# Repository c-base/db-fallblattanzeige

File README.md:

# db-fallblattanzeige
A Fallblattfahrzielanzeige of the Deutsche Bahn

  - [Demo video](https://www.youtube.com/watch?v=KNWKdqRn240)
  - [Hackaday Project](https://hackaday.io/project/9070-fallblattfahrzielanzeige-of-s-bahn-berlin)

Daemon ist unter: https://github.com/c-base/db-fallblattanzeige-web/roloboxd/

Web-Interface-Repo ist unter: https://github.com/c-base/db-fallblattanzeige-web

Architektur-Skizze: https://www.dropbox.com/s/tzrm99uehv5yp3d/whiteboard.png?dl=0

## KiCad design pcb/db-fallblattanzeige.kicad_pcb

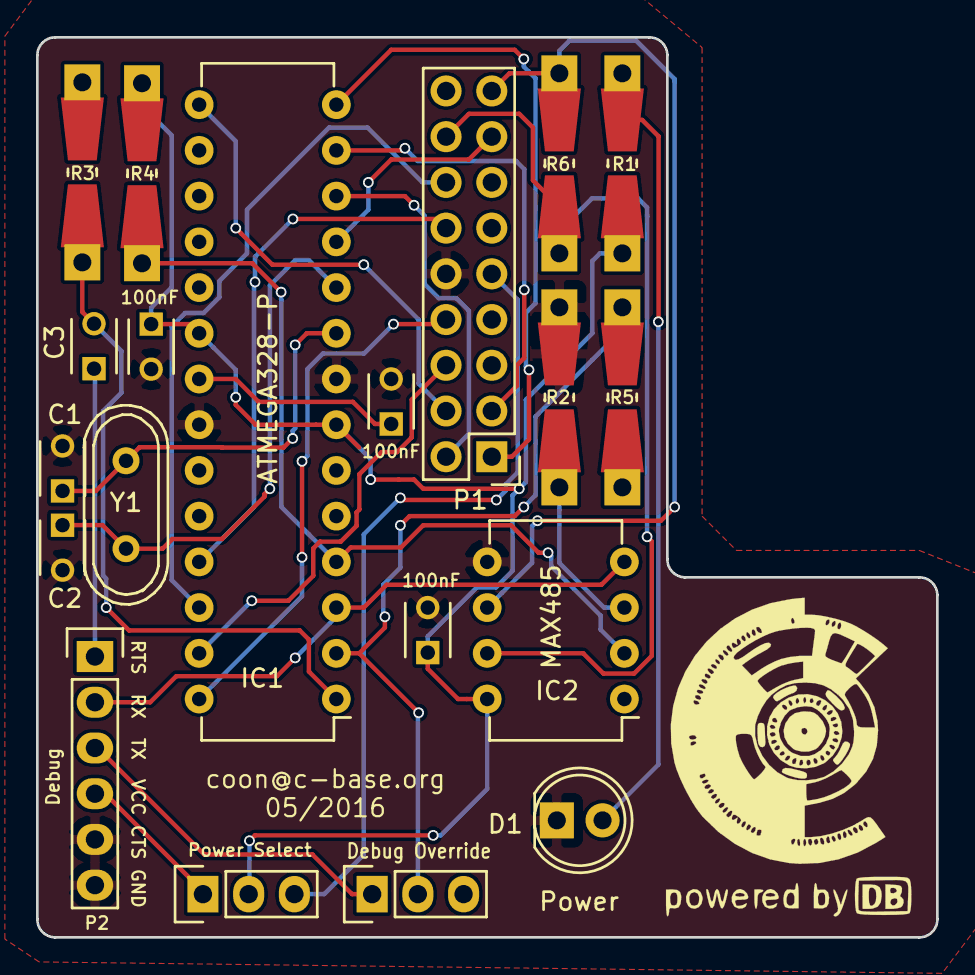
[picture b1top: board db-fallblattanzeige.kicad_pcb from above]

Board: 2 copper layers, 50.0 x 50.0 mm, 20 parts (0 on the bottom side), 27 nets.

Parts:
100nF, 100nF#2, 100nF#3: C; C_Disc_D3_P2.5
C1, C2: 22pF; C_Disc_D3_P2.5
C3: 100nF; C_Disc_D3_P2.5
D1: Power LED (Green); LED-5MM
IC1: ATMEGA328-P; DIP-28_W7.62mm
IC2: MAX485; DIP-8_W7.62mm
JP1: Debug Override; Pin_Header_Straight_1x03
JP2: Power Select; Pin_Header_Straight_1x03
P1: ZiLOG_3562_FBM_V2.02
P2: FTDI_header; Pin_Header_Straight_1x06
R1: 150; Resistor_SMD+THTuniversal_0805to1206_RM10_HandSoldering
R2, R4: 4.7K; Resistor_SMD+THTuniversal_0805to1206_RM10_HandSoldering
R3: 10K; Resistor_SMD+THTuniversal_0805to1206_RM10_HandSoldering
R5: 1K; Resistor_SMD+THTuniversal_0805to1206_RM10_HandSoldering
R6: 120; Resistor_SMD+THTuniversal_0805to1206_RM10_HandSoldering
Y1: Crystal; Crystal_HC49-U_Vertical

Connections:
+5VA: JP2.1, P2.4
+5VD: JP2.3, P1.5
/BUS_MINUS: IC2.7, P1.11, R6.1
/BUS_PLUS: IC2.6, P1.9, R6.2
/IR_IN: IC1.11, P1.8
/Motor: IC1.15, P1.17
/PWR_IR1: IC1.26, P1.12
/PWR_IR2: IC1.25, P1.13
/SCL: IC1.28, P1.15
/SDA: IC1.27, P1.16
/SR_CP: IC1.13, P1.2
/SR_DATA: IC1.14, P1.1
/~SR_LATCH: IC1.12, P1.18
GND: 100nF.2, 100nF#2.2, 100nF#3.2, C1.2, C2.2, D1.1, IC1.8, IC1.22, IC2.5, P1.14, P2.5, P2.6, R2.2
unnamed: 100nF.1, IC1.21
unnamed: C1.1, IC1.9, Y1.1
unnamed: C2.1, IC1.10, Y1.2
unnamed: C3.1, P2.1
unnamed: C3.2, IC1.1, R3.2
unnamed: D1.2, R1.2
unnamed: IC1.2, JP1.2, R5.2
unnamed: IC1.3, IC2.4, P2.2
unnamed: IC1.4, IC2.2, R4.1
unnamed: IC1.5, IC2.3, R2.1
unnamed: IC2.1, R5.1
unnamed: JP1.1, P2.3
VCC: 100nF#2.1, 100nF#3.1, IC1.7, IC1.20, IC2.8, JP2.2, R1.1, R3.1, R4.2

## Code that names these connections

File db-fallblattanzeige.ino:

// DB-Fallblattanzeige 
// 21.01.2016
//
// Authors: uk, coon

#include <Wire.h>

// Pins
const int PIN_SENSORS_IN = 5;  // PD5
const int PIN_SR_LATCH   = 6;  // PD6
const int PIN_SR_CP      = 7;  // PD7
const int PIN_SR_DATA    = 8;  // PB0
const int PIN_MOTOR      = 9;  // PB1
const int PIN_IR_ROTARY  = A2; // PC2
const int PIN_IR_ORIGIN  = A3; // PC3

// constants
const int I2C_EEPROM_ADDR = 0x50; // A0, A1, A2 are all on ground.
const int ORIGIN_OFFSET = 5; // TODO: read from EEPROM later

void waitForRotaryQuarters(int quarters) {
  for(int i = 0; i < quarters; i++) {
    while(!digitalRead(PIN_SENSORS_IN)); // wait for first high
    while(digitalRead(PIN_SENSORS_IN));  // wait for low
    while(!digitalRead(PIN_SENSORS_IN)); // wait for second high
  }
}

void flipCards(int numCards) {
  digitalWrite(PIN_IR_ROTARY, HIGH);
  digitalWrite(PIN_MOTOR, LOW);
  
  for(int i = 0; i < numCards; i++)
    waitForRotaryQuarters(1);
    
  digitalWrite(PIN_MOTOR, HIGH);
  digitalWrite(PIN_IR_ROTARY, LOW);
}

void spinToOrigin() {
  digitalWrite(PIN_IR_ORIGIN, HIGH);
  digitalWrite(PIN_MOTOR, LOW);

  while(digitalRead(PIN_SENSORS_IN));  // skip first high value
  while(!digitalRead(PIN_SENSORS_IN)); // wait for home  
  while(digitalRead(PIN_SENSORS_IN));  // wait for end of home
  
  digitalWrite(PIN_IR_ORIGIN, LOW);
  
  flipCards(ORIGIN_OFFSET); // flip some additional cards, if needed
  
  digitalWrite(PIN_MOTOR, HIGH);
}

void initI2cEeprom() {
  Wire.setClock(0); // set to lowest possible speed

  Wire.beginTransmission(I2C_EEPROM_ADDR); // Chosen base address
  Wire.write(0); // send MSB of the address
  Wire.write(0); // send LSB of the address
  
  if(byte error = Wire.endTransmission())
    Serial.println("I2C-EEPROM did not respond!");
  else {
    delay(100);
    Wire.requestFrom(I2C_EEPROM_ADDR, 20);

    Serial.println("Waiting for data from EEPROM...");
    while(!Wire.available());

    Serial.print("Data: ");

    for(int i = 0; i < 20; i++) {
      if(i % 15 == 0)
        Serial.println("");
    
      byte b = Wire.read();
      Serial.print("0x");
      Serial.print(String(b, HEX));
      Serial.print(" ");
    }
  }
}

void setup() {
  digitalWrite(PIN_MOTOR, HIGH);
  digitalWrite(PIN_IR_ORIGIN, LOW);
  digitalWrite(PIN_IR_ROTARY, LOW);
  
  pinMode(PIN_SENSORS_IN, INPUT);
  pinMode(PIN_SR_LATCH,   OUTPUT);
  pinMode(PIN_SR_CP,      OUTPUT);
  pinMode(PIN_SR_DATA,    INPUT);
  pinMode(PIN_MOTOR,      OUTPUT);
  pinMode(PIN_IR_ORIGIN,  OUTPUT);
  pinMode(PIN_IR_ROTARY,  OUTPUT);
  
  Serial.begin(9600);

  initI2cEeprom();
  spinToOrigin();
}

void loop() {
  if (Serial.available() > 0) {
    int numCards = Serial.parseInt();
    if(numCards > 0)
      flipCards(numCards);
    else
      spinToOrigin();
  }
}

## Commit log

2016-01-04 it works!
2016-01-05 Added demo video
2016-01-05 hackaday project link added
2016-01-05 better markdown formating
2016-01-05 Add serial control
2016-01-05 add origin offset
2016-01-19 modified code for prototype pcb
2016-01-21 add basic I2C eeprom support but seems buggy...
2016-01-23 device address can now be read
2016-01-25 add kicad project
2016-01-26 add some part to schematic
2016-01-26 add library for RS485 chip
2016-01-26 progress on schematic + add bus cable schematic
2016-01-27 add missing files
2016-01-27 rename 'bus_cable' schematic to 'device_board'
2016-01-27 kicad: add some parts to device board
2016-01-30 add details like ac power and opto triac
2016-01-30 add some connections to bus connector
2016-02-02 kicad: add BUS_UNKNOWN circuit
2016-02-03 kicad: corrected wiring
2016-02-09 added MAX810
2016-02-12 kicad: add some wires to MAX485
2016-02-14 kicad: finished RS485 wiring
2016-02-14 kicad: rework of communication circuits
2016-02-14 arduino: added... things
2016-02-14 add parking position to tx jumper
2016-02-21 kicad: removed schmitt trigger
2016-02-22 kicad: annotate and fixing errors
2016-02-22 kicad: forgotten files...
2016-02-22 add netlist and footprint
2016-02-24 improved pcb layout
2016-02-26 fix crystal wiring, blocking caps
2016-02-27 arduino: add \n terminator
2016-02-28 kicad: completed routing
2016-02-28 add logo + FTDI header
2016-02-28 kicad: add some descriptions on silk
2016-02-28 kicad: add ground plane
2016-02-28 kicad: final version
2016-03-22 kicad: some work on revision 1
2016-03-22 corrected zilog footprint and silk
2016-04-04 finished revision 1
2016-04-30 fix 180° bug + R3/R4 swap (Rev2)
2016-06-18 add protocol for daemon
